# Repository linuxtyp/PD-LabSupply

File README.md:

# PD-LabSupply
A 100W Laboratory Power Supply that uses USBC-PowerDelivery Protocol

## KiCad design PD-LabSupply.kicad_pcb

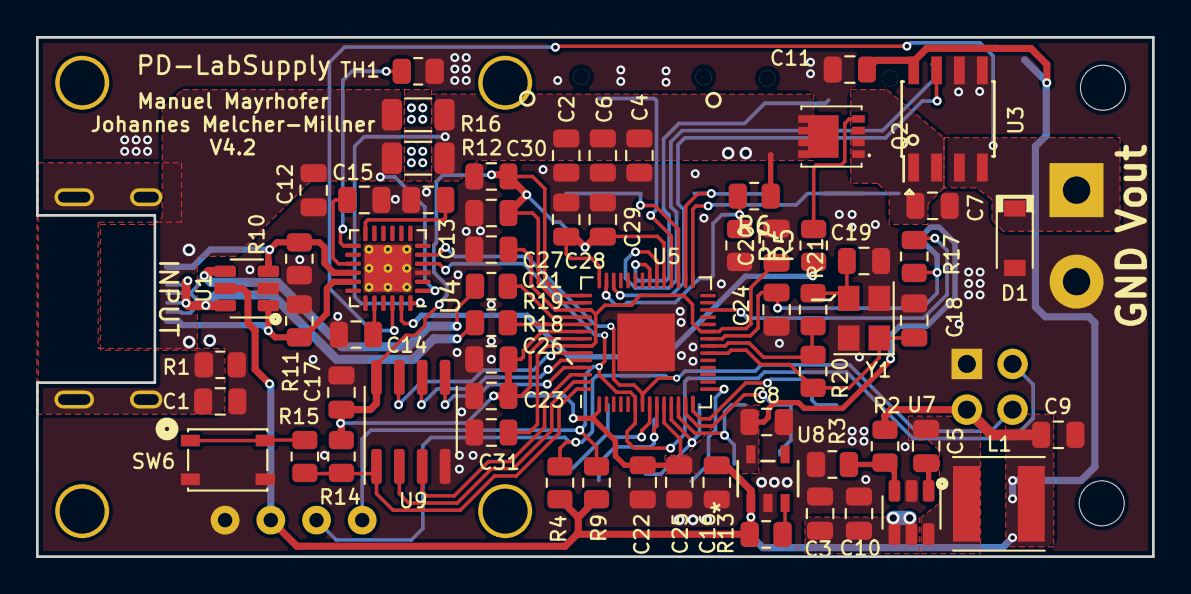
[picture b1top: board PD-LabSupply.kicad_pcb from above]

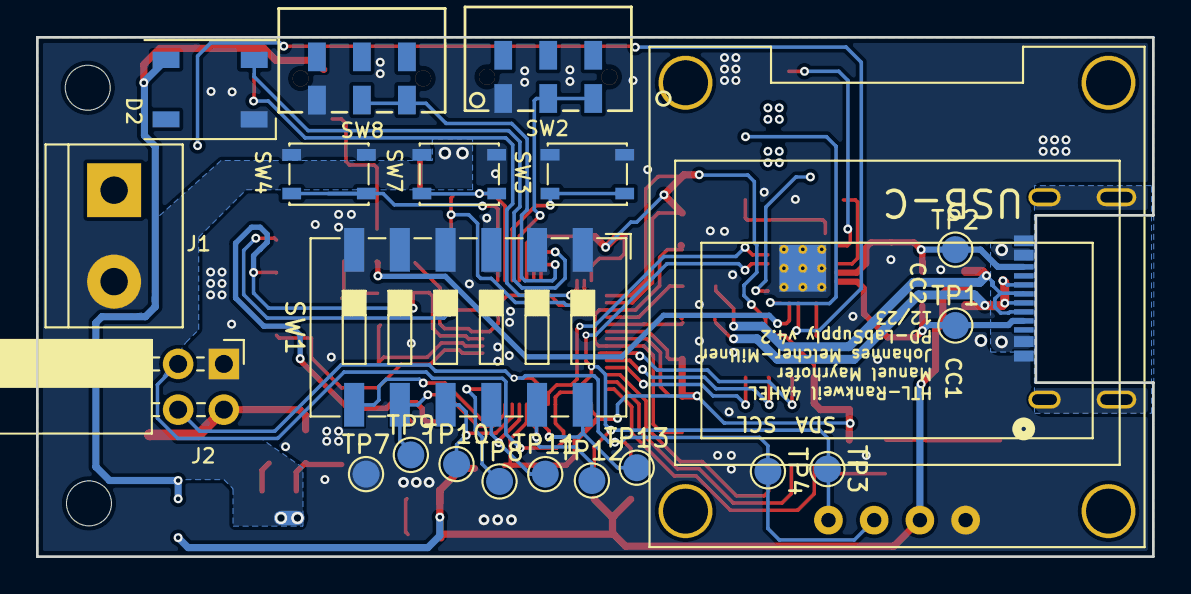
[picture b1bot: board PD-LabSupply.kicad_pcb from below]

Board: 2 copper layers, 62.0 x 28.8 mm, 88 parts (22 on the bottom side), 53 nets.

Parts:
C1: 10nF; C_0805_2012Metric
C2, C4, C6, C7, C8, C11, C14, C16, C21, C28, C29: 1uF 50V; C_0805_2012Metric
C3: 2.2uF 50V; C_0805_2012Metric
C5, C17, C20, C22, C23, C24, C25, C26, C27, C30, C31: 0.1uF; C_0805_2012Metric
C9, C10: 22uF 50V; C_0805_2012Metric
C12: 10u 50V; C_0805_2012Metric
C13, C15: 100nF; C_0805_2012Metric
C18, C19: 18pF; C_0805_2012Metric
D1: SMF22A; D_SOD-123
D2: WS2812B; LED_WS2812B_PLCC4_5.0x5.0mm_P3.2mm
H2, H4: MountingHole; MountingHole_2.5mm
J1: Conn_01x02; TerminalBlock_bornier-2_P5.08mm
J2: Conn_02x02_Odd_Even; PinSocket_2x02_P2.54mm_Horizontal
J3: USB4520-03-0-A; CONN12_USB4520-03-0-A_GCT
L1: 15uH; L_Taiyo-Yuden_MD-5050
Q2: DMN3008SFGQ-7; DMG7401SFG13
R1, R13, R14, R17: 10k; R_0805_2012Metric
R2: 120k; R_0805_2012Metric
R3: 22k; R_0805_2012Metric
R4, R9, R10, R11: 5.1k; R_0805_2012Metric
R5, R15: 1k; R_0805_2012Metric
R6, R7: X; R_0805_2012Metric
R12, R16: 20m; R_1206_3216Metric
R18, R19: 27; R_0805_2012Metric
R20: DNP; R_0805_2012Metric
R21: 1K; R_0805_2012Metric
SW1: SW_DIP_x06; SW_DIP_SPSTx06_Slide_9.78x17.42mm_W8.61mm_P2.54mm
SW2, SW8: JS202011JAQN
SW3, SW4, SW6, SW7: SW_Push; SW_SPST_PTS810
TH1: NTC-10k; R_0805_2012Metric
TP1, TP2, TP3, TP4, TP7, TP8, TP9, TP10, TP11, TP12, TP13: TestPoint; TestPoint_Pad_D1.5mm
U1: SRV05-4; SOT-23-6
U3: TMCS1108; SOIC-8_3.9x4.9mm_Pitch1.27mm
U4: AP33772
U5: RP2040; QFN-56-1EP_7x7mm_P0.4mm_EP3.2x3.2mm
U6: oledSym; SSD1306_0.96_Oled
U7: LMR54410; SOT-23-6
U8: AP2112K-3.3TRG1; SOT_RG1_DIO
U9: W25Q16JVSSIQ; SOIC-8_3.9x4.9mm_P1.27mm
Y1: Crystal_GND24; Crystal_SMD_3225-4Pin_3.2x2.5mm

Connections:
+3V3: C8.1, C17.1, C22.1, C23.1, C24.1, C25.1, C26.1, C27.1, C28.1, C29.1, C30.1, R14.1, R17.1, U5.1 (IOVDD), U5.10 (IOVDD), U5.22 (IOVDD), U5.33 (IOVDD), U5.42 (IOVDD), U5.43 (ADC_AVDD), U5.44 (VREG_IN), U5.48 (USB_VDD), U5.49 (IOVDD), U8.5 (VOUT), U9.8 (VCC)
+5V: C9.1, C11.1, C16.1, D2.1 (VDD), J2.3, L1.2, R2.1, R4.1, R9.1, R13.1, U1.5 (VP), U3.8 (VS), U6.2 (VCC), U8.1 (VIN)
/+1.1V: C20.1, C21.1, C31.1, U5.23 (DVDD), U5.45 (VREG_VOUT), U5.50 (DVDD)
/SW: C5.2, L1.1, U7.6 (SW)
BTN_DOWN: SW4.2, U5.29 (GPIO18)
BTN_SEL: SW7.2, U5.30 (GPIO19)
BTN_UP: SW3.2, U5.31 (GPIO20)
CC1: J3.CC1, R11.1, TP1.1, U1.1 (IO1), U4.17 (CC1)
CC2: J3.CC2, R10.1, TP2.1, U1.3 (IO2), U4.16 (CC2)
D_N: J3.D_N (D-), R19.2, U1.4 (IO3)
D_P: J3.D_P (D+), R18.1, U1.6 (IO4)
EN5V: SW1.12, TP13.1, U5.8 (GPIO6)
EN9V: SW1.11, TP12.1, U5.9 (GPIO7)
EN12V: SW1.10, TP11.1, U5.11 (GPIO8)
EN15V: SW1.9, TP10.1, U5.12 (GPIO9)
EN20V: SW1.8, TP9.1, U5.13 (GPIO10)
ENOUT: R5.1, U4.23 (PWR_EN)
ENPSU: SW1.7, U5.14 (GPIO11)
EXT_OUT: TP8.1, U5.15 (GPIO12)
GND: C1.2, C2.2, C3.2, C4.2, C6.2, C7.2, C8.2, C9.2, C10.2, C11.2, C12.2, C13.2, C14.2, C15.2, C16.2, C17.2, C18.2, C19.2, C20.2, C21.2, C22.2, C23.2, C24.2, C25.2, C26.2, C27.2, C28.2, C29.2, C30.2, C31.2, D1.2 (A), D2.3 (VSS), J1.2, J2.1, J3.GND, R1.2, R3.2, R7.2, R10.2, R11.2, SW1.1, SW1.2, SW1.3, SW1.4, SW1.5, SW1.6, SW2.3, SW3.1, SW4.1, SW6.1, SW7.1, SW8.3, TH1.2, TP7.1, U1.2 (VN), U3.5 (GND), U3.6 (NC), U4.3 (GND), U4.25 (EP), U5.57 (GND), U6.1 (GND), U7.2 (GND), U8.2 (GND), U9.4 (GND), Y1.2, Y1.4
HALL_ADC: U3.7 (VOUT), U5.40 (GPIO28_ADC2)
HALL_IN: C7.1, Q2.S, U3.1 (IN+), U3.2 (IN+)
LED: D2.4 (DIN), U5.34 (GPIO22)
unnamed: C1.1, J3.SHIELD, R1.1
unnamed: C19.1, R21.2, Y1.3
unnamed: Q2.G, R5.2
unnamed: R15.1, SW6.2
unnamed: C15.1, U4.15 (IFB)
unnamed: TH1.1, U4.13 (OTP)
unnamed: C13.1, U4.12 (V3VD)
unnamed: C14.1, U4.20 (V5V)
unnamed: R17.2, U5.26 (RUN)
unnamed: R19.1, U5.46 (USB_DM)
unnamed: R18.2, U5.47 (USB_DP)
unnamed: C5.1, U7.1 (CB)
unnamed: R2.2, R3.1, U7.3 (FB)
unnamed: R13.2, U8.3 (EN)
OUT: D1.1 (K), J1.1, U3.3 (IN-), U3.4 (IN4), U4.22 (VBUS)
QSPI_SCLK: U5.52 (QSPI_SCLK), U9.6 (CLK)
QSPI_SD0: U5.53 (QSPI_SD0), U9.5 (DI(IO0))
QSPI_SD1: U5.55 (QSPI_SD1), U9.2 (DO(IO1))
QSPI_SD2: U5.54 (QSPI_SD2), U9.3 (~WP(IO2))
QSPI_SD3: U5.51 (QSPI_SD3), U9.7 (~HOLD/RESET(IO3))
QSPI_SS: R14.2, R15.2, U5.56 (QSPI_SS), U9.1 (~CS)
SCL: J2.4, R4.2, TP4.1, U4.5 (SCL), U5.7 (GPIO5), U6.3 (SCL)
SDA: J2.2, R9.2, TP3.1, U4.4 (SDA), U5.6 (GPIO4), U6.4 (SDA)
SW_OUT: SW8.1, SW8.2, U5.35 (GPIO23)
SW_VA: SW2.1, SW2.2, U5.32 (GPIO21)
VBUS: C2.1, C3.1, C4.1, C6.1, C10.1, Q2.D, R6.1, R12.1, R16.1, U4.24 (VCC), U7.4 (EN), U7.5 (VIN)
VDD: C12.1, J3.VBUS, R12.2, R16.2, U4.1 (ISENP)
V_ADC: R6.2, R7.1, U5.41 (GPIO29_ADC3)
XIN: C18.1, R20.2, U5.20 (XIN), Y1.1
XOUT: R20.1, R21.1, U5.21 (XOUT)

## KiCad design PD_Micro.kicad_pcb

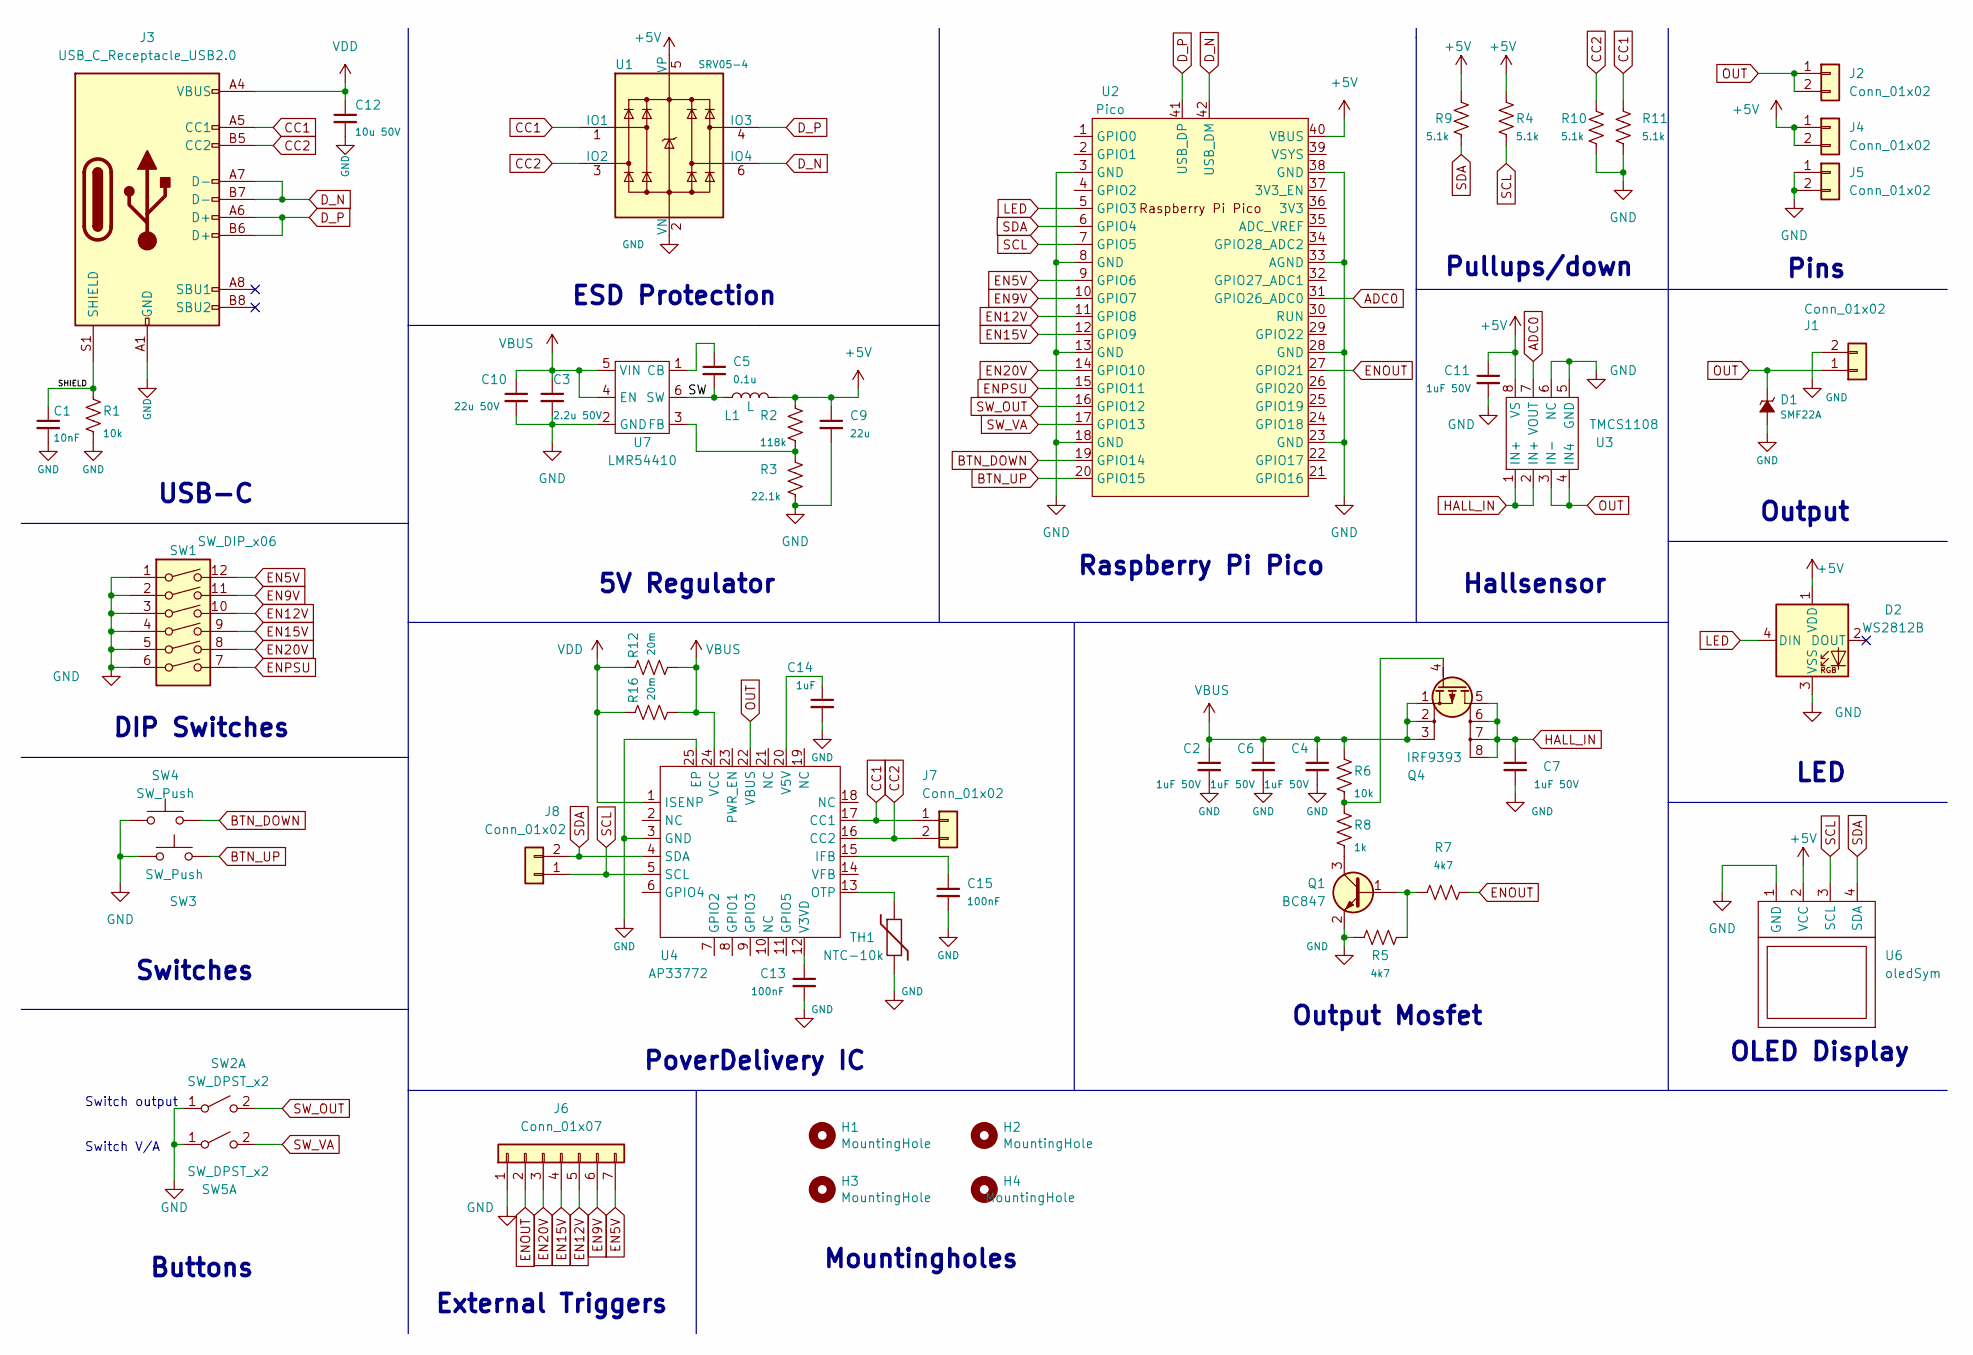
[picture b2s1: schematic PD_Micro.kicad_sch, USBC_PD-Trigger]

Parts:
C1: 10nF; C_0805_2012Metric
C2, C4, C6, C7, C11: 1uF 50V; C_0805_2012Metric
C3: 2.2u 50V; C_0805_2012Metric
C5: 0.1u; C_0805_2012Metric
C9: 22u; C_0805_2012Metric
C10: 22u 50V; C_0805_2012Metric
C12: 10u 50V; C_0805_2012Metric
C13, C15: 100nF; C_0805_2012Metric
C14: 1uF; C_0805_2012Metric
D1: SMF22A; D_SOD-123
D2: WS2812B; LED_WS2812B_PLCC4_5.0x5.0mm_P3.2mm
H1, H2, H3, H4: MountingHole; D1_8_PAD
J1: Conn_01x02; TerminalBlock_bornier-2_P5.08mm
J2, J4, J5, J7, J8: Conn_01x02; PinHeader_1x02_P2.54mm_Vertical
J3: USB_C_Receptacle_USB2.0; USB_C_Receptacle_JAE_DX07S016JA1R1500
J6: Conn_01x07; PinSocket_1x07_P2.54mm_Vertical
L1: L; L_4012
Q1: BC847; SOT-23
Q4: IRF9393; SOIC-8_3.9x4.9mm_P1.27mm
R1, R6: 10k; R_0805_2012Metric
R2: 118k; R_0805_2012Metric
R3: 22.1k; R_0805_2012Metric
R4, R9, R10, R11: 5.1k; R_0805_2012Metric
R5, R7: 4k7; R_0805_2012Metric
R8: 1k; R_0805_2012Metric
R12, R16: 20m; C_1206_3216Metric
SW1: SW_DIP_x06; SW_DIP_SPSTx06_Slide_9.78x17.42mm_W7.62mm_P2.54mm
SW2, SW5: SW_DPST_x2; SW_SPDT_PCM12
SW3, SW4: SW_Push; SW_SPST_TL3305B
TH1: NTC-10k; R_0805_2012Metric
U1: SRV05-4; SOT-23-6
U2: Pico; RPi_Pico_SMD_TH
U3: TMCS1108; SOIC-8_3.9x4.9mm_P1.27mm
U4: AP33772; WQFN-24-1EP_4x4mm_P0.5mm_EP2.6x2.6mm_ThermalVias
U6: oledSym; 128x64OLED
U7: LMR54410; SOT-23-6

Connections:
+5V: C9.1, C11.1, D2.1 (VDD), J4.1, J4.2, L1.2, R2.1, R4.1, R9.1, U1.5 (VP), U2.40 (VBUS), U3.8 (VS), U6.2 (VCC)
/SHIELD: C1.1, J3.S1 (SHIELD), R1.1
/SW: C5.2, L1.1, U7.6 (SW)
ADC0: U2.31 (GPIO26_ADC0), U3.7 (VOUT)
BTN_DOWN: SW4.2, U2.19 (GPIO14)
BTN_UP: SW3.2, U2.20 (GPIO15)
CC1: J3.A5 (CC1), J7.1, R11.1, U1.1 (IO1), U4.17 (CC1)
CC2: J3.B5 (CC2), J7.2, R10.1, U1.3 (IO2), U4.16 (CC2)
D_N: J3.A7 (D-), J3.B7 (D-), U1.6 (IO4), U2.42 (USB_DM)
D_P: J3.A6 (D+), J3.B6 (D+), U1.4 (IO3), U2.41 (USB_DP)
EN5V: J6.7, SW1.12, U2.9 (GPIO6)
EN9V: J6.6, SW1.11, U2.10 (GPIO7)
EN12V: J6.5, SW1.10, U2.11 (GPIO8)
EN15V: J6.4, SW1.9, U2.12 (GPIO9)
EN20V: J6.3, SW1.8, U2.14 (GPIO10)
ENOUT: J6.2, R7.1, U2.27 (GPIO21)
ENPSU: SW1.7, U2.15 (GPIO11)
GND: C1.2, C2.2, C3.2, C4.2, C6.2, C7.2, C9.2, C10.2, C11.2, C12.2, C13.2, C14.2, C15.2, D1.2 (A), D2.3 (VSS), J1.2, J3.A1 (GND), J3.A12 (GND), J3.B1 (GND), J3.B12 (GND), J5.1, J5.2, J6.1, Q1.2 (E), R1.2, R3.2, R5.1, R10.2, R11.2, SW1.1, SW1.2, SW1.3, SW1.4, SW1.5, SW1.6, SW2.1 (A), SW3.1, SW4.1, SW5.1 (A), TH1.2, U1.2 (VN), U2.3 (GND), U2.8 (GND), U2.13 (GND), U2.18 (GND), U2.23 (GND), U2.28 (GND), U2.33 (AGND), U2.38 (GND), U3.5 (GND), U3.6 (NC), U4.3 (GND), U4.25 (EP), U6.1 (GND), U7.2 (GND)
HALL_IN: C7.1, Q4.5 (D), Q4.6 (D), Q4.7 (D), Q4.8 (D), U3.1 (IN+), U3.2 (IN+)
LED: D2.4 (DIN), U2.5 (GPIO3)
unnamed: Q1.1 (B), R5.2, R7.2
unnamed: Q1.3 (C), R8.2
unnamed: Q4.4 (G), R6.2, R8.1
unnamed: C15.1, U4.15 (IFB)
unnamed: TH1.1, U4.13 (OTP)
unnamed: C13.1, U4.12 (V3VD)
unnamed: C14.1, U4.20 (V5V)
unnamed: C5.1, U7.1 (CB)
unnamed: R2.2, R3.1, U7.3 (FB)
OUT: D1.1 (K), J1.1, J2.1, J2.2, U3.3 (IN-), U3.4 (IN4), U4.22 (VBUS)
SCL: J8.1, R4.2, U2.7 (GPIO5), U4.5 (SCL), U6.3 (SCL)
SDA: J8.2, R9.2, U2.6 (GPIO4), U4.4 (SDA), U6.4 (SDA)
SW_OUT: SW2.2 (B), U2.16 (GPIO12)
SW_VA: SW5.2 (B), U2.17 (GPIO13)
VBUS: C2.1, C3.1, C4.1, C6.1, C10.1, Q4.1 (S), Q4.2 (S), Q4.3 (S), R6.1, R12.1, R16.1, U4.24 (VCC), U7.4 (EN), U7.5 (VIN)
VDD: C12.1, J3.A4 (VBUS), J3.A9 (VBUS), J3.B4 (VBUS), J3.B9 (VBUS), R12.2, R16.2, U4.1 (ISENP)

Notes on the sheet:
Switch V/A
External Triggers
Pins
Output Mosfet
ESD Protection
LED
Pullups/down
Switches
Buttons
Output
Switch output
5V Regulator
OLED Display
PoverDelivery IC
Raspberry Pi Pico
Hallsensor
DIP Switches
Mountingholes
USB-C

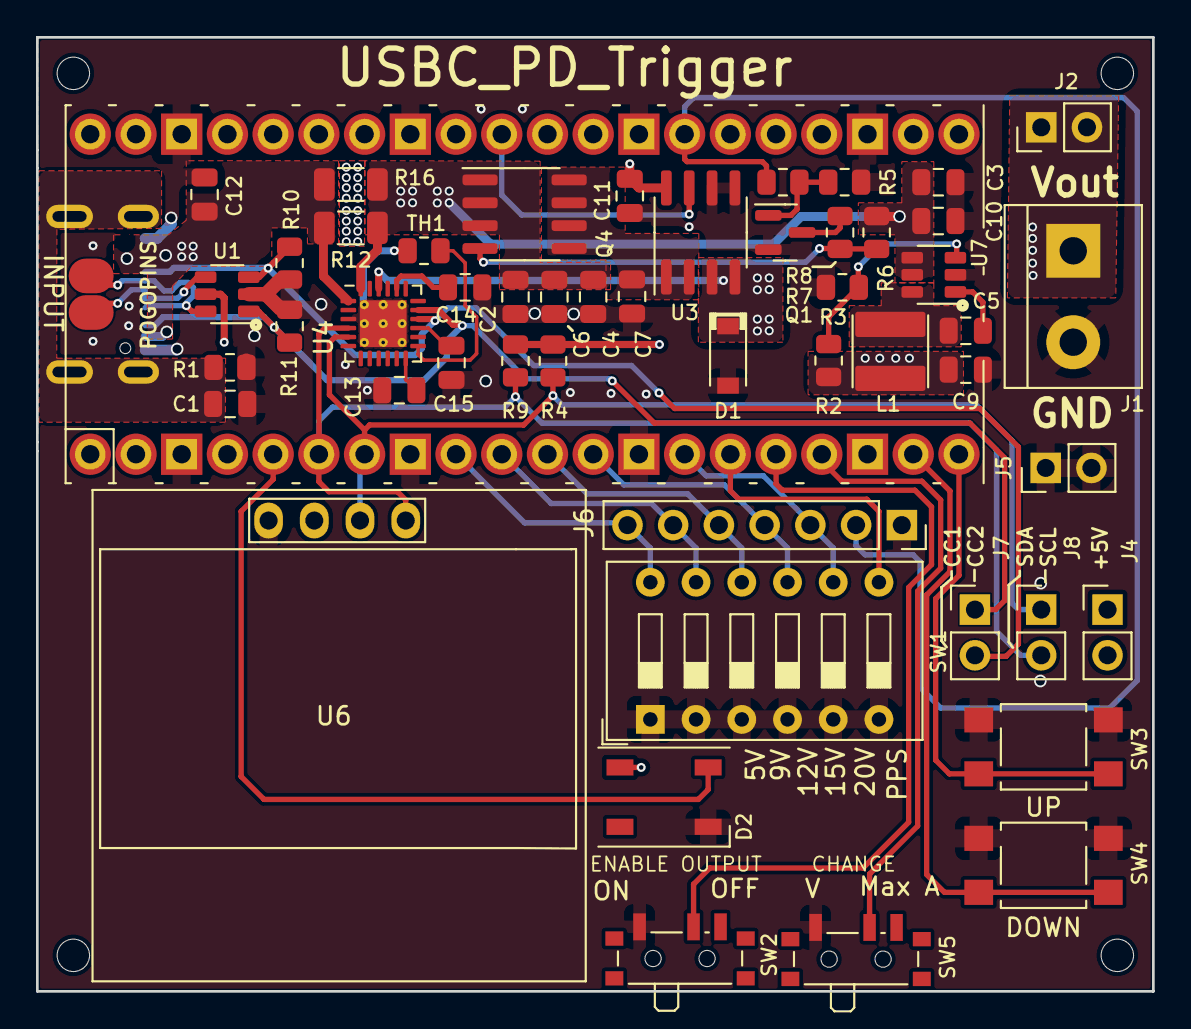
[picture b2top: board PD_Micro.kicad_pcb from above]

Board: 2 copper layers, 62.0 x 53.0 mm, 56 parts (1 on the bottom side), 36 nets.

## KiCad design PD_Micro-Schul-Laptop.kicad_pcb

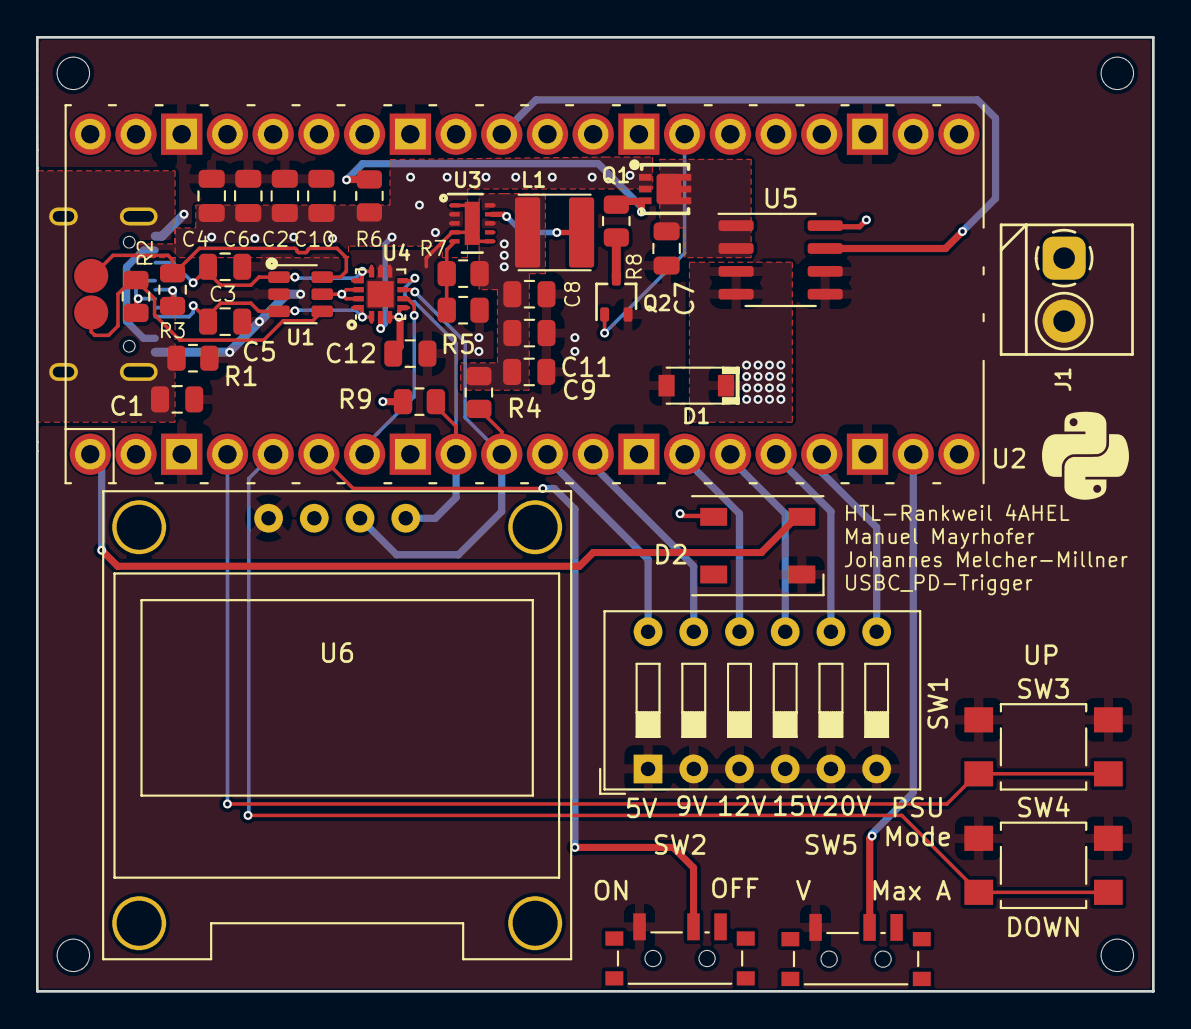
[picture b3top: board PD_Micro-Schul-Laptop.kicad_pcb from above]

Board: 2 copper layers, 62.0 x 53.0 mm, 43 parts (1 on the bottom side), 32 nets.

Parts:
C1: 10nF; C_0805_2012Metric
C2, C4, C6, C7: 1uF 50V; C_0805_2012Metric
C3, C5: 330pF; C_0805_2012Metric
C8, C9, C11: 10uF; C_0805_2012Metric
C10, C12: 0.1uF; C_0805_2012Metric
D1: SMF22A; D_SOD-123
D2: WS2812B; LED_WS2812B_PLCC4_5.0x5.0mm_P3.2mm
H1, H2, H3, H4: MountingHole; D1_8_PAD
J1: Conn_01x02; TerminalBlock_3.5mm_2P
L1: 10uH; L_4012
Q1: DMP3017SFK; DFN-2523-6
Q2: DTC143E; SOT-323_SC-70
R1, R6: 10k; R_0805_2012Metric
R2, R3: 22R; R_0805_2012Metric
R4, R9: 2k; R_0805_2012Metric
R5: 51k; R_0805_2012Metric
R7: 270k; R_0805_2012Metric
R8: 1k; R_0805_2012Metric
SW1: SW_DIP_x06; SW_DIP_SPSTx06_Slide_9.78x17.42mm_W7.62mm_P2.54mm
SW2, SW5: SW_DPST_x2; SW_SPDT_PCM12
SW3, SW4: SW_Push; SW_SPST_TL3305B
U1: SRV05-4; SOT-23-6
U2: Pico; RPi_Pico_SMD_TH
U3: TPS62175DQC; WSON-10-1EP_2x3mm_P0.5mm_EP0.84x2.4mm
U4: FUSB302BMPX; WQFN-14-1EP_2.5x2.5mm_P0.5mm_EP1.45x1.45mm
U5: ACS723xLCTR-10AB; SOIC-8_3.9x4.9mm_P1.27mm
U6: oledSym; SSD1306_0.96_Oled
USB1: HRO-TYPE-C-31-M-12

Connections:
+5V: C8.1, C9.1, C11.1, C12.1, D2.1 (VDD), L1.2, R4.1, R7.1, R9.1, U1.5 (VP), U2.40 (VBUS), U3.8 (~SLEEP), U3.10 (VOS), U4.3 (VDD), U4.4 (VDD), U4.12 (VCONN), U4.13 (VCONN), U5.8 (VCC), U6.2 (VCC)
/CC1: C5.2, U1.3 (IO2), U4.1 (CC2), U4.14 (CC2), USB1.4 (CC1)
/CC2: C3.2, U1.1 (IO1), U4.10 (CC1), U4.11 (CC1), USB1.10 (CC2)
/D1_N: R3.1, U1.6 (IO4), U2.42 (USB_DM)
/D1_P: R2.1, U1.4 (IO3), U2.41 (USB_DP)
/D_N: R3.2, USB1.5 (DN2), USB1.7 (DN1)
/D_P: R2.2, USB1.6 (DP1), USB1.8 (DP2)
/HALL_IN: C7.1, Q1.4 (D), Q1.5 (D), Q1.6 (D), U5.1 (IP+), U5.2 (IP+)
/OUT: D1.1 (K), J1.1, U5.3 (IP-), U5.4 (IP-)
/SHIELD: C1.1, R1.1, USB1.13 (SHIELD)
/SW1: L1.1, U3.9 (SW)
ADC0: U2.31 (GPIO26_ADC0), U5.7 (VIOUT)
EN5V: SW1.12, U2.11 (GPIO8)
EN9V: SW1.11, U2.12 (GPIO9)
EN12V: SW1.10, U2.14 (GPIO10)
EN15V: SW1.9, U2.15 (GPIO11)
EN20V: SW1.8, U2.16 (GPIO12)
ENOUT: Q2.1 (B), U2.27 (GPIO21)
ENPSU: SW1.7, U2.17 (GPIO13)
GND: C1.2, C2.2, C3.1, C4.2, C5.1, C6.2, C7.2, C8.2, C9.2, C10.2, C11.2, C12.2, D1.2 (A), D2.3 (VSS), J1.2, Q2.2 (E), R1.2, R5.2, SW1.1, SW1.2, SW1.3, SW1.4, SW1.5, SW1.6, SW2.1 (A), SW3.1, SW4.1, SW5.1 (A), U1.2 (VN), U2.3 (GND), U2.8 (GND), U2.13 (GND), U2.18 (GND), U2.23 (GND), U2.28 (GND), U2.33 (AGND), U2.38 (GND), U3.1 (PGND), U3.4 (NC), U3.6 (AGND), U3.11 (PAD), U4.8 (GND), U4.9 (GND), U4.15 (GND), U5.5 (GND), U5.6 (BW_SEL), U6.1 (GND), USB1.1 (GND), USB1.12 (GND)
INT_N: U2.7 (GPIO5), U4.5 (INT_N)
unnamed: D2.4 (DIN), U2.1 (GPIO0)
unnamed: Q1.3 (G), R6.2, R8.1
unnamed: Q2.3 (C), R8.2
unnamed: SW2.2 (B), U2.6 (GPIO4)
unnamed: SW5.2 (B), U2.19 (GPIO14)
unnamed: SW3.2, U2.4 (GPIO2)
unnamed: SW4.2, U2.5 (GPIO3)
unnamed: R5.1, R7.2, U3.5 (FB)
SCL: R4.2, U2.10 (GPIO7), U4.6 (SCL), U6.3 (SCL)
SDA: R9.2, U2.9 (GPIO6), U4.7 (SDA), U6.4 (SDA)
VBUS: C2.1, C4.1, C6.1, C10.1, Q1.1 (S), Q1.2 (S), R6.1, U3.2 (VIN), U3.3 (EN), U4.2 (VBUS), USB1.2 (VBUS), USB1.11 (VBUS)

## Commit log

2023-09-21 initial
2023-09-22 incl pico
2023-09-22 librarys
2023-09-22 testcommit
2023-09-22 pico
2023-09-23 new pcb
2023-09-23 merge1
2023-09-23 merge2
2023-09-23 pcb started
2023-09-23 pico-symbol
2023-09-24 no drc errors
2023-09-25 no drcs plus input devices
2023-09-25 differential-pair
2023-09-25 differential-pairs
2023-09-27 finished pcb
2023-09-28 silk
2023-10-11 bevore silkscreen delete
2023-10-11 v1 sent to zudrell
2023-10-11 small fix
2023-10-12 bevore rebuild
2023-10-12 schematic finished
2023-10-12 sch finished, parts placed
2023-10-12 pcb v2 finished
2023-10-19 v2.1
2023-10-25 v2.2
2023-11-09 a few fixes
2023-11-17 usbc-save
2023-11-20 view
2023-11-22 save
2023-11-22 pcb save
2023-11-24 v3.1 finished
2023-11-25 finished
2023-11-27 final
2023-11-27 rename
2023-11-29 fine
2023-12-01 new version
2023-12-03 layout finished
2023-12-03 layout almost complete
2023-12-08 fertig
2023-12-10 wirklich mol fertig
2023-12-14 bestellung
2024-01-31 New Files
2024-01-31 The working version
2024-01-31 New Documentation
2024-01-31 Bilder
2024-01-31 hardware
2024-02-23 final version working

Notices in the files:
parts and their libraries:
Copyright 2016 Accelerated Designs. All rights reserved.
